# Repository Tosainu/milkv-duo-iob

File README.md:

# Milk-V IO Board

Milk-V Duo IO Board - KiCad project files.

## License

- [CC BY 4.0](https://creativecommons.org/licenses/by/4.0/)

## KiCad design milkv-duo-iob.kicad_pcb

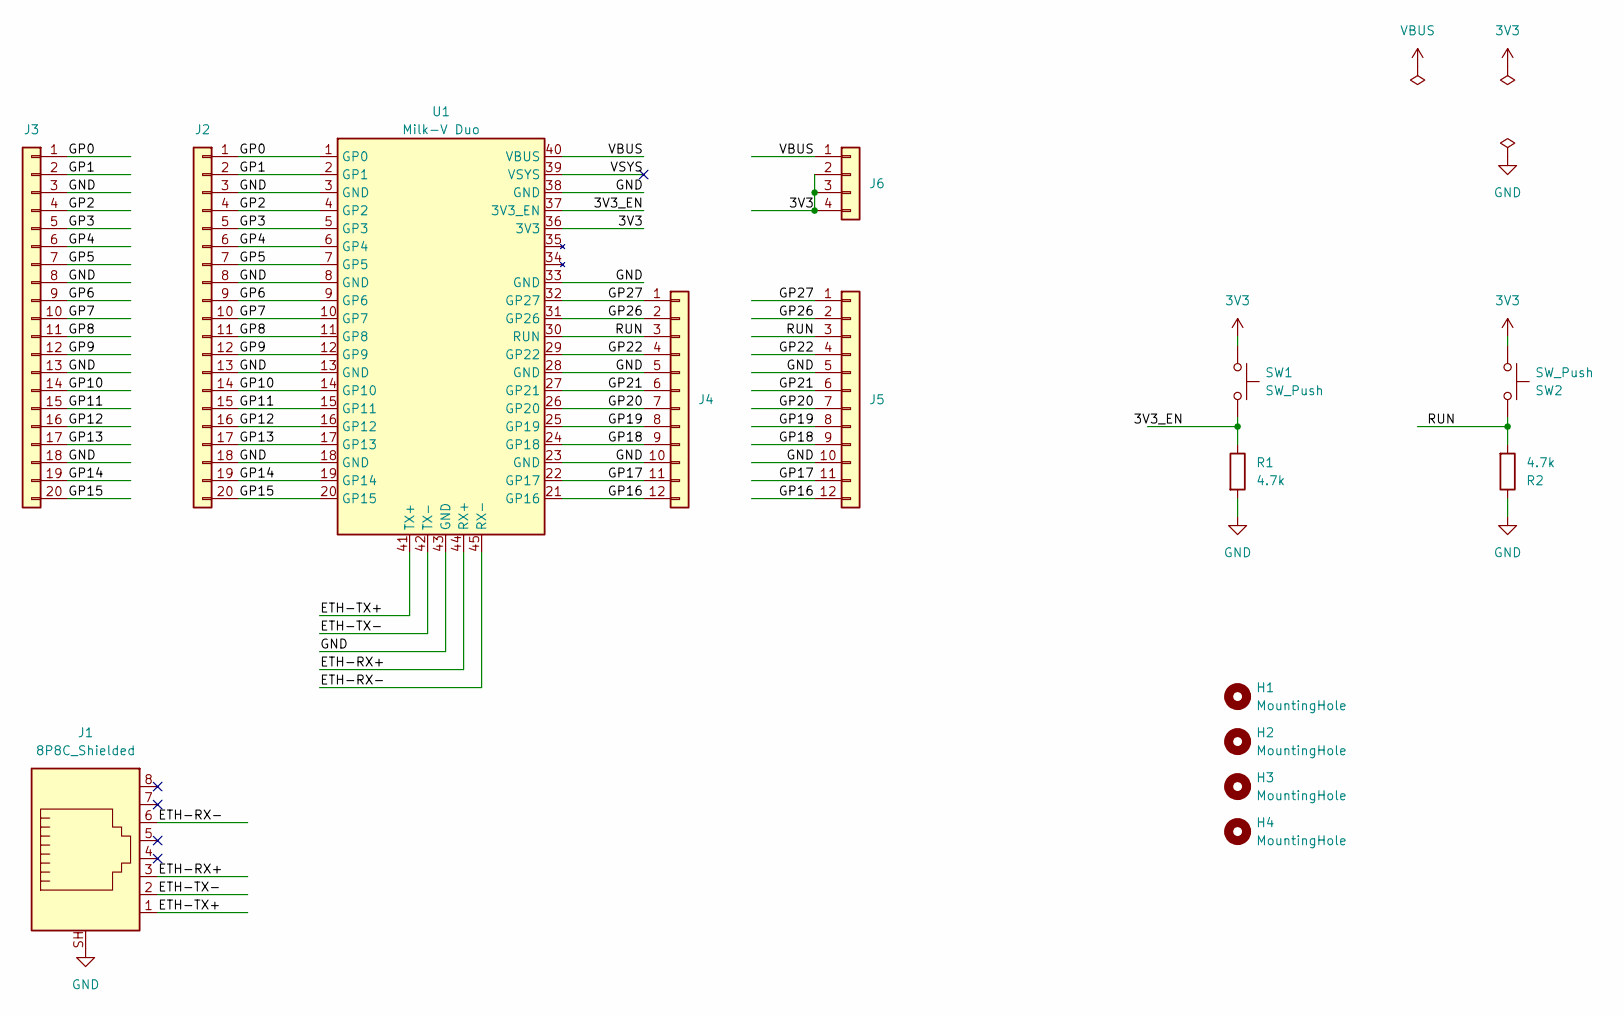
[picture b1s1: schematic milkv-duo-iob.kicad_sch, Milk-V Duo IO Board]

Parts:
H1, H2, H3, H4: MountingHole; MountingHole_2.7mm_M2.5
J1: 8P8C_Shielded; RJ45_Neltron_7810-XPXC
J2, J3: Conn_01x20; PinHeader_1x20_P2.54mm_Vertical
J4, J5: Conn_01x12; PinHeader_1x12_P2.54mm_Vertical
J6: Conn_01x04; PinHeader_1x04_P2.54mm_Vertical
R1, R2: 4.7k; R_0805_2012Metric_Pad1.20x1.40mm_HandSolder
SW1, SW2: SW_Push; Button_Tactile_SPST_Jianfu_TVAF06-A020B-R
U1: Milk-V Duo; Milk-V_Duo_THT

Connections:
3V3: J6.2, J6.3, J6.4, SW1.1, SW2.2, U1.36 (3V3)
/3V3_EN: R1.1, SW1.2, U1.37 (3V3_EN)
/ETH-RX+: J1.3, U1.44 (RX+)
/ETH-RX-: J1.6, U1.45 (RX-)
/ETH-TX+: J1.1, U1.41 (TX+)
/ETH-TX-: J1.2, U1.42 (TX-)
/GP0: J2.1, J3.1, U1.1 (GP0)
/GP1: J2.2, J3.2, U1.2 (GP1)
/GP2: J2.4, J3.4, U1.4 (GP2)
/GP3: J2.5, J3.5, U1.5 (GP3)
/GP4: J2.6, J3.6, U1.6 (GP4)
/GP5: J2.7, J3.7, U1.7 (GP5)
/GP6: J2.9, J3.9, U1.9 (GP6)
/GP7: J2.10, J3.10, U1.10 (GP7)
/GP8: J2.11, J3.11, U1.11 (GP8)
/GP9: J2.12, J3.12, U1.12 (GP9)
/GP10: J2.14, J3.14, U1.14 (GP10)
/GP11: J2.15, J3.15, U1.15 (GP11)
/GP12: J2.16, J3.16, U1.16 (GP12)
/GP13: J2.17, J3.17, U1.17 (GP13)
/GP14: J2.19, J3.19, U1.19 (GP14)
/GP15: J2.20, J3.20, U1.20 (GP15)
/GP16: J4.12, J5.12, U1.21 (GP16)
/GP17: J4.11, J5.11, U1.22 (GP17)
/GP18: J4.9, J5.9, U1.24 (GP18)
/GP19: J4.8, J5.8, U1.25 (GP19)
/GP20: J4.7, J5.7, U1.26 (GP20)
/GP21: J4.6, J5.6, U1.27 (GP21)
/GP22: J4.4, J5.4, U1.29 (GP22)
/GP26: J4.2, J5.2, U1.31 (GP26)
/GP27: J4.1, J5.1, U1.32 (GP27)
/RUN: J4.3, J5.3, R2.2, SW2.1, U1.30 (RUN)
/VSYS: U1.39 (VSYS)
GND: J1.SH, J2.3, J2.8, J2.13, J2.18, J3.3, J3.8, J3.13, J3.18, J4.5, J4.10, J5.5, J5.10, R1.2, R2.1, U1.3 (GND), U1.8 (GND), U1.13 (GND), U1.18 (GND), U1.23 (GND), U1.28 (GND), U1.33 (GND), U1.38 (GND), U1.43 (GND)
VBUS: J6.1, U1.40 (VBUS)

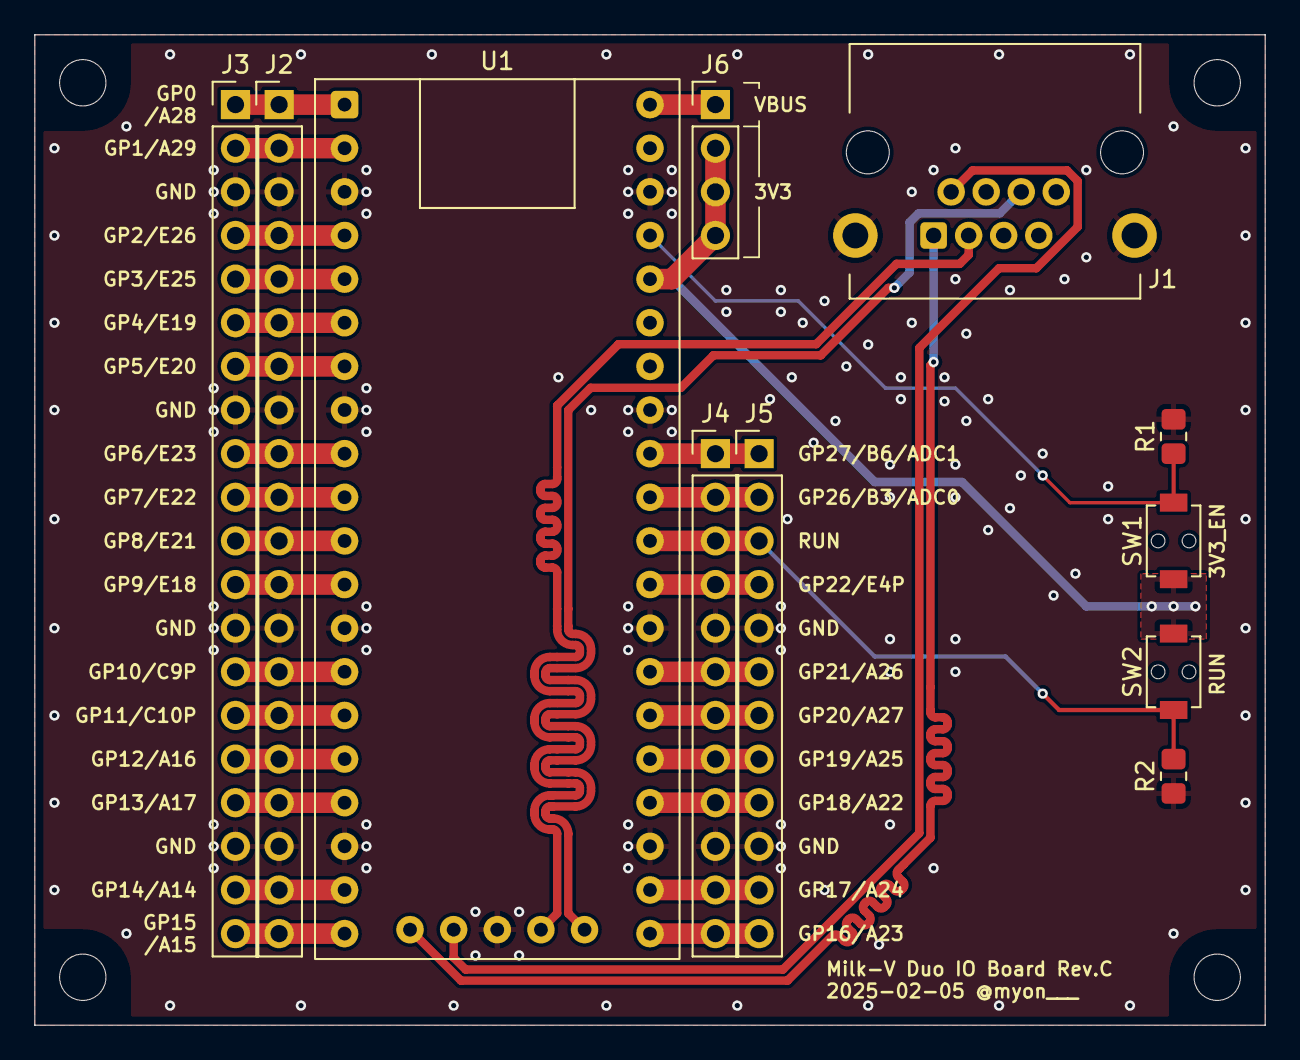
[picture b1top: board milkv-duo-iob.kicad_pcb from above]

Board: 2 copper layers, 71.6 x 57.7 mm, 15 parts (0 on the bottom side), 34 nets.

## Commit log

2024-09-22 Rev.A
2024-09-22 Rev.A (今度こそ)
    Milk-V Duo の横幅間違えてるし、公式配布の CAD 見ると Ethernet のピンが若干ずれているのも判明
    Symbox/footprint 作って対応
2024-09-24 スポーク角度とか調整
2024-09-24 Track width 0.2 -> 0.25
2024-09-24 Rev.B
2025-02-04 Add missing files
2025-02-04 Improve impedance of Etherer (hopefully)
